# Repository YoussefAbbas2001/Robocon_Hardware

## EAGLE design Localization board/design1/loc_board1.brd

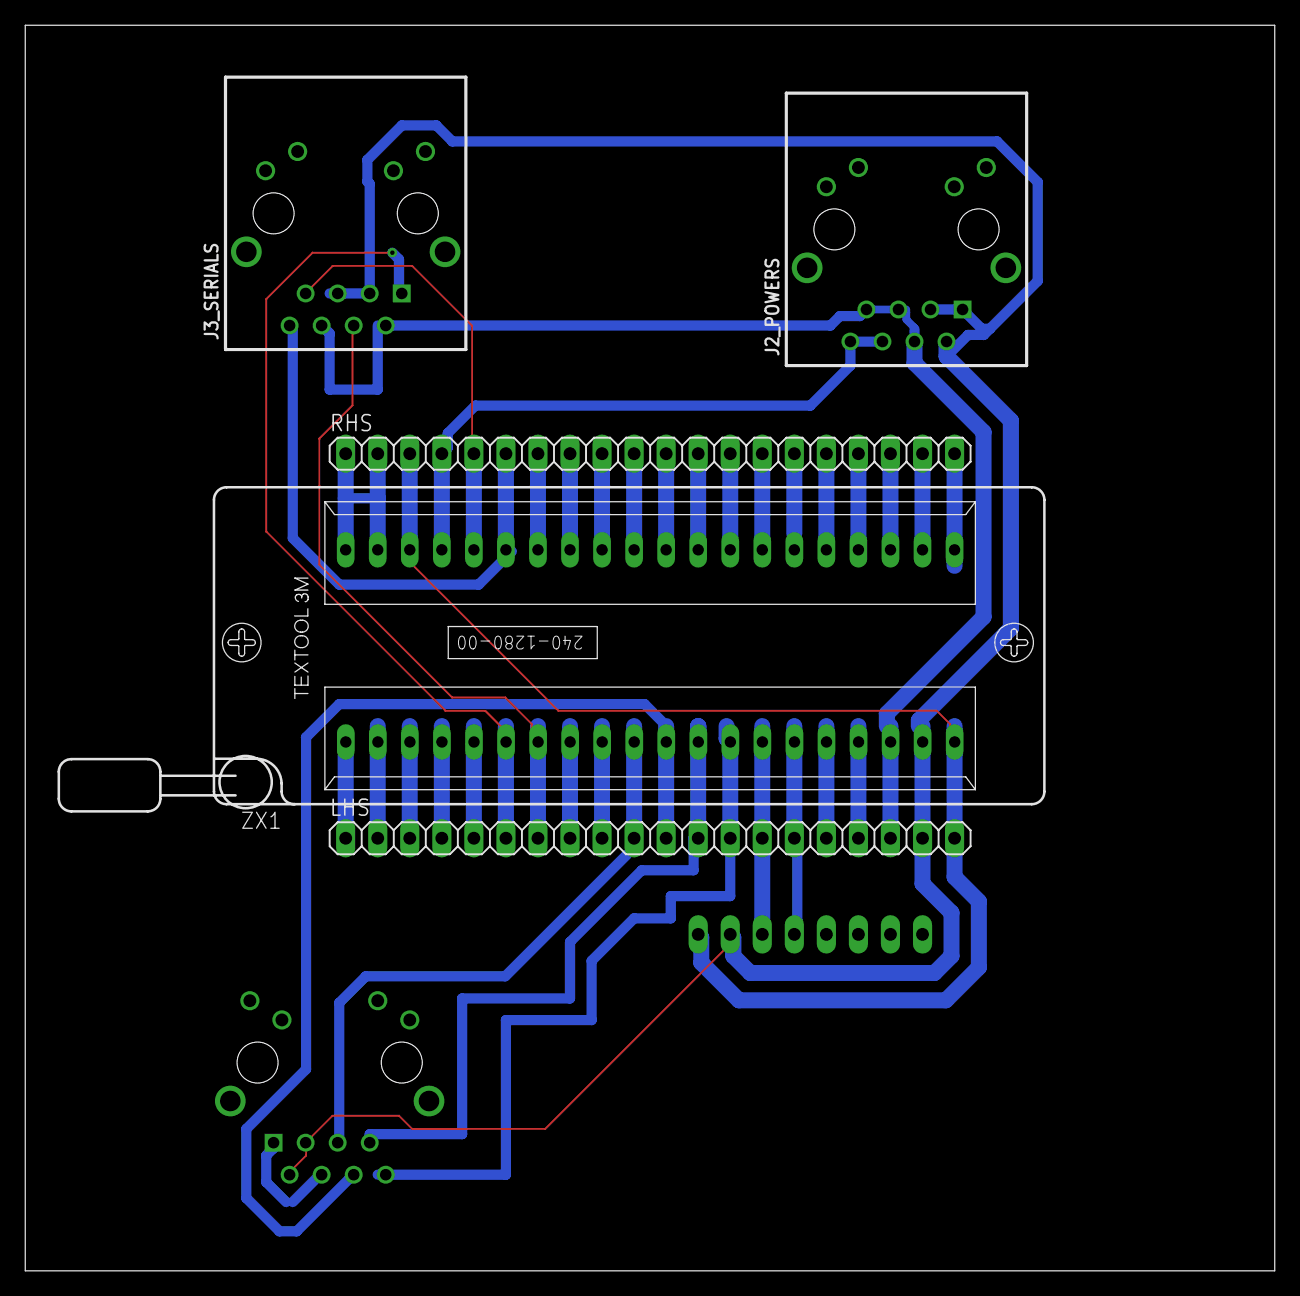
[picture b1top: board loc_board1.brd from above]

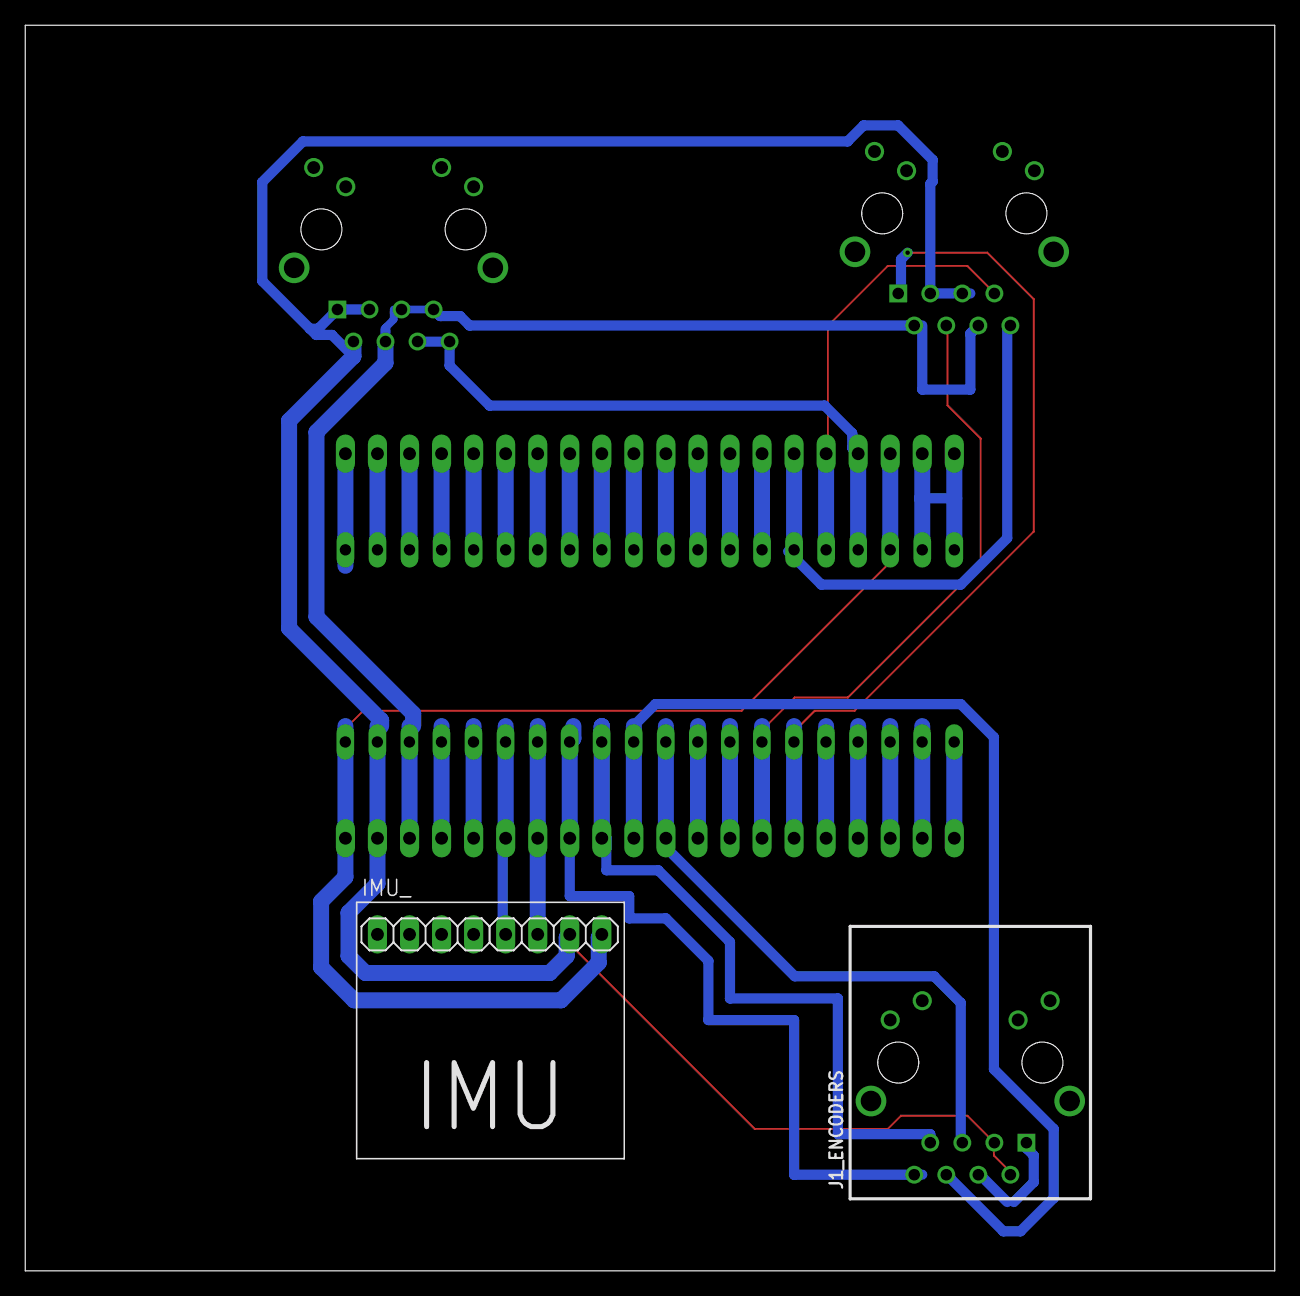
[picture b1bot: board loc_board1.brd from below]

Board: 2 copper layers, 99.0 x 98.7 mm, 7 parts (2 on the bottom side), 39 nets.

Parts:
IMU_: IMU_ROBOCON_GY521; IMU_GY521
J1_ENCODERS, J2_POWERS, J3_SERIALS: RJ45_METAL_LEDS; J0-A/B/F
LHS: 1X20
RHS: 1X20
ZX1: ZIF_401280; 240-1280-00-0602J

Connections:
3.3V: IMU_.VCC, LHS.20, RHS.3, ZX1.20, ZX1.38
5V: J2_POWERS.4, J2_POWERS.5, J2_POWERS.7, J3_SERIALS.2, J3_SERIALS.6, LHS.18, ZX1.18
GND: IMU_.GND, J1_ENCODERS.2, J1_ENCODERS.3, J2_POWERS.1, J2_POWERS.2, J2_POWERS.3, J3_SERIALS.3, LHS.19, ZX1.19
unnamed: J1_ENCODERS.1, J1_ENCODERS.4
unnamed: RHS.1, RHS.2, ZX1.39, ZX1.40
PA0: RHS.16, ZX1.25
PA1: RHS.15, ZX1.26
PA2: RHS.14, ZX1.27
PA3: RHS.13, ZX1.28
PA4: RHS.12, ZX1.29
PA5: RHS.11, ZX1.30
PA6: RHS.10, ZX1.31
PA7: RHS.9, ZX1.32
PA8: LHS.5, ZX1.5
PA9: J3_SERIALS.1, LHS.6, ZX1.6
PA10: J3_SERIALS.4, LHS.7, ZX1.7
PA11: LHS.8, ZX1.8
PA12: LHS.9, ZX1.9
PA15: J1_ENCODERS.5, LHS.10, ZX1.10
PB0: RHS.8, ZX1.33
PB1: RHS.7, ZX1.34
PB3: J1_ENCODERS.6, LHS.11, ZX1.11
PB4: J1_ENCODERS.7, LHS.12, ZX1.12
PB5: LHS.13, ZX1.13
PB6: IMU_.SCL, LHS.14, ZX1.14
PB7: IMU_.SDA, LHS.15, ZX1.15
PB8: LHS.16, ZX1.16
PB9: LHS.17, ZX1.17
PB10: J3_SERIALS.8, RHS.6, ZX1.35
PB11: J3_SERIALS.7, RHS.5, ZX1.36
PB12: LHS.1, ZX1.1
PB13: LHS.2, ZX1.2
PB14: LHS.3, ZX1.3
PB15: LHS.4, ZX1.4
PC13: RHS.19, ZX1.22
PC14: RHS.18, ZX1.23
PC15: RHS.17, ZX1.24
RESET: J2_POWERS.6, J2_POWERS.8, RHS.4, ZX1.37
VBAT: RHS.20, ZX1.21

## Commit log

2022-02-05 design1 first
